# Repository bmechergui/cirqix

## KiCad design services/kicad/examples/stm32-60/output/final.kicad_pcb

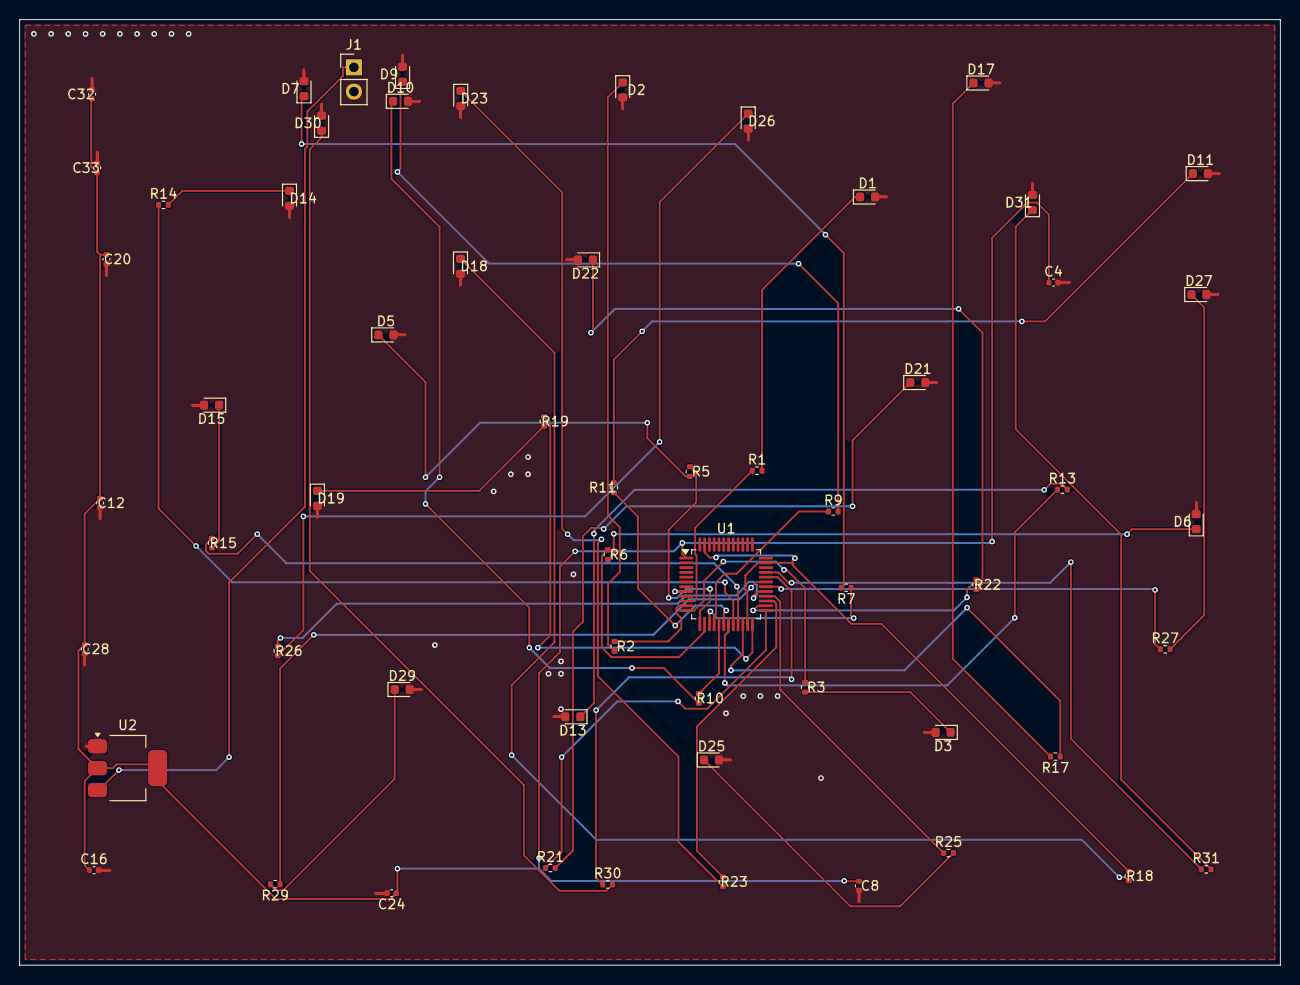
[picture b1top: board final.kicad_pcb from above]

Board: 2 copper layers, 132.0 x 99.0 mm, 60 parts (0 on the bottom side), 51 nets.

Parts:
C4, C8, C12, C16, C20, C24, C28, C32, C33: 100nF; C_0402_1005Metric
D1, D2, D3, D5, D6, D7, D9, D10, D11, D13, D14, D15, D17, D18, D19, D21, D22, D23, D25, D26, D27, D29, D30, D31: LED; LED_0603_1608Metric
J1: 5V; PinHeader_1x02_P2.54mm_Vertical
R1, R2, R3, R5, R6, R7, R9, R10, R11, R13, R14, R15, R17, R18, R19, R21, R22, R23, R25, R26, R27, R29, R30, R31: 330; R_0402_1005Metric
U1: STM32F103C8T6; LQFP-48_7x7mm_P0.5mm
U2: AMS1117-3.3; SOT-223-3_TabPin2

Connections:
+3.3V: C4.1, C8.1, C12.1, C16.1, C20.1, C24.1, C28.1, C32.1, C33.1, U1.1, U2.2
GND: C4.2, C8.2, C12.2, C16.2, C20.2, C24.2, C28.2, C32.2, C33.2, D1.2, D2.2, D3.2, D5.2, D6.2, D7.2, D9.2, D10.2, D11.2, D13.2, D14.2, D15.2, D17.2, D18.2, D19.2, D21.2, D22.2, D23.2, D25.2, D26.2, D27.2, D29.2, D30.2, D31.2, J1.2, U1.8, U2.1
GPIO1: R1.1, U1.10
GPIO2: R2.1, U1.11
GPIO3: R3.1, U1.12
GPIO5: R5.1, U1.13
GPIO6: R6.1, U1.14
GPIO7: R7.1, U1.15
GPIO9: R9.1, U1.16
GPIO10: R10.1, U1.17
GPIO11: R11.1, U1.18
GPIO13: R13.1, U1.19
GPIO14: R14.1, U1.20
GPIO15: R15.1, U1.21
GPIO17: R17.1, U1.22
GPIO18: R18.1, U1.23, U1.35, U1.47
GPIO19: R19.1, U1.24
GPIO21: R21.1, U1.25
GPIO22: R22.1, U1.26
GPIO23: R23.1, U1.27
GPIO25: R25.1, U1.28
GPIO26: R26.1, U1.29
GPIO27: R27.1, U1.30
GPIO29: R29.1, U1.31
GPIO30: R30.1, U1.32
GPIO31: R31.1, U1.33
LED1: D1.1, R1.2
LED2: D2.1, R2.2
LED3: D3.1, R3.2
LED5: D5.1, R5.2
LED6: D6.1, R6.2
LED7: D7.1, R7.2
LED9: D9.1, R9.2
LED10: D10.1, R10.2
LED11: D11.1, R11.2
LED13: D13.1, R13.2
LED14: D14.1, R14.2
LED15: D15.1, R15.2
LED17: D17.1, R17.2
LED18: D18.1, R18.2
LED19: D19.1, R19.2
LED21: D21.1, R21.2
LED22: D22.1, R22.2
LED23: D23.1, R23.2
LED25: D25.1, R25.2
LED26: D26.1, R26.2
LED27: D27.1, R27.2
LED29: D29.1, R29.2
LED30: D30.1, R30.2
LED31: D31.1, R31.2
VIN: J1.1, U2.3

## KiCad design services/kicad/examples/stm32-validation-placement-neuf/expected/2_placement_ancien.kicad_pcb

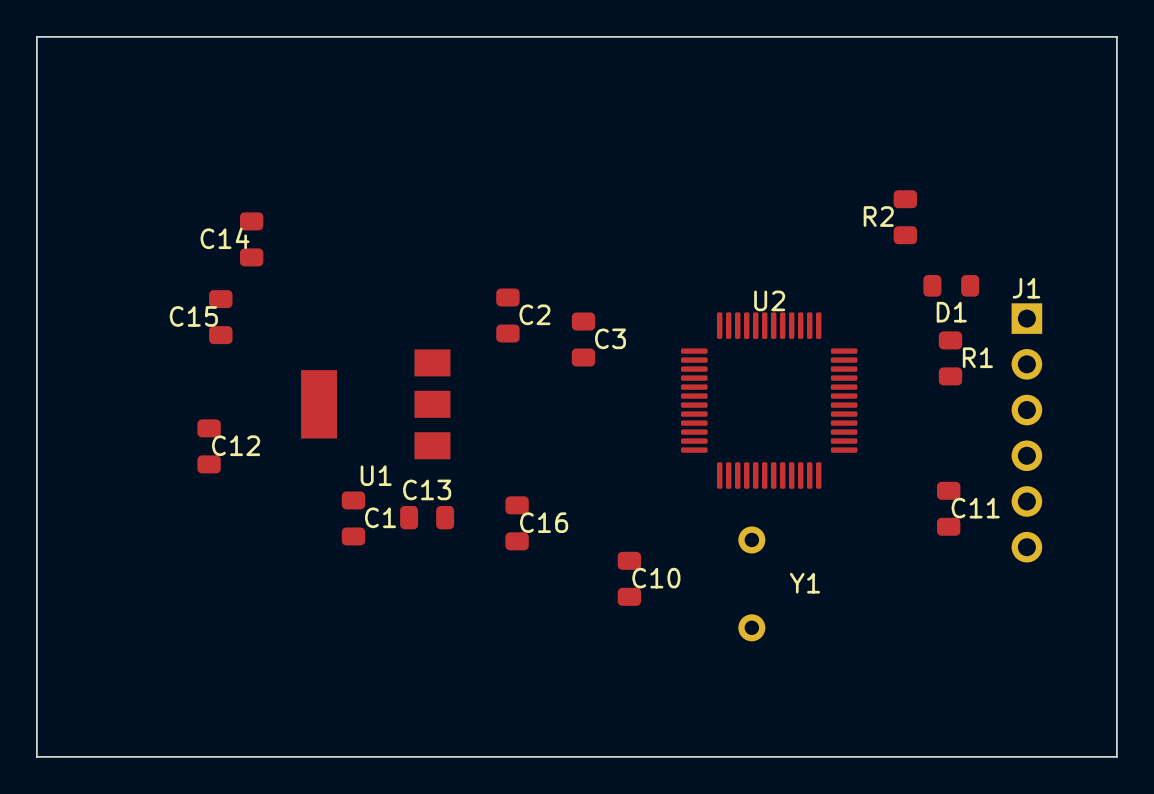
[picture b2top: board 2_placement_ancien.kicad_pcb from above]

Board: 2 copper layers, 60.0 x 40.0 mm, 17 parts (0 on the bottom side), 12 nets, no tracks yet.

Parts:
C1, C2: 10uF; C_0805_2012Metric
C3, C12, C13, C14, C15: 100nF; C_0805_2012Metric
C10, C11: 20pF; C_0805_2012Metric
C16: 4.7uF; C_0805_2012Metric
D1: LED; LED_0805_2012Metric
J1: SWD; PinHeader_1x06_P2.54mm_Vertical
R1: 330R; R_0805_2012Metric
R2: 10k; R_0805_2012Metric
U1: AMS1117-3.3; SOT-223-3_TabPin2
U2: STM32F103C8T6; LQFP-48_7x7mm_P0.5mm
Y1: 8MHz; Crystal_HC49-4H_Vertical

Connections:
+3.3V: C2.1, C3.1, C12.1, C13.1, C14.1, C15.1, C16.1, J1.1, R1.1, U1.3, U2.1, U2.9, U2.24, U2.36, U2.48
+5V: C1.1, U1.1
BOOT0: R2.1, U2.44
GND: C1.2, C2.2, C3.2, C10.2, C11.2, C12.2, C13.2, C14.2, C15.2, C16.2, J1.6, R2.2, U1.2, U2.8, U2.23, U2.35, U2.47
LED_K: D1.1, R1.2
NRST: J1.5, U2.7
OSC_IN: C10.1, U2.5, Y1.1
OSC_OUT: C11.1, U2.6, Y1.2
SWCLK: J1.3, U2.37
SWDIO: J1.2, U2.34
SWO: J1.4, U2.39
USER_LED: D1.2, U2.25
